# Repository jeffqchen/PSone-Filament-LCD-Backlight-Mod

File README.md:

# PSone Filament LCD Backlight Mod

The official PSone LCD screen has a fragile backlight system. The inverter and the CCFL tube could kick the bucket on itself. Sometimes you can't even figure out what went wrong with the backlight system. It's also nearly impossible to find the exact replacement parts at a reasonable price, even if you managed to figure it out.

Previously, there were multiple attempts of similar mods. But they all used singular LEDs, and resulted in uneven backlight that's difficult to look at. This new type of flexible filament LED provides the uniformity as good as the CCFL tube, and is very easy to manipulate. More importantly, they are very affordable.

So here is my solution, just in case you are facing the dilemma (however, by all means, please try to diagnose and fix the original system if possible).

This design takes the 7.5V from the power input, runs it through an NPN amplifier, to feed power through two 3V flexible filament LED strips and some current-limiting resistors, controlled by the 5V_CON signal from the console.

Please note these values were fine tuned and do not match the perfect calculations. Somehow these filament LED strips do not drop the claimed voltage and I had to reduce the value of the current-limiting resistors to make them emit enough light. I did let the system run for an extended period of time to make sure it would last. The operation temperature was still much lower than the original design.

----------
## Parts

- [PCB](https://oshpark.com/shared_projects/M3fZRLg5)

- BSR14 NPN Amplifier / SOT23-3 - [Link](https://github.com/jeffqchen/JeffParts/blob/main/Components/BSR14%20NPN%20Amplifier/info.md)

- [2x] Flexible Filament LED Strips, 130mm, DC 3V, Cold White 6500K - [Link](https://github.com/jeffqchen/JeffParts/blob/main/Parts/Flexible%20Filament%20LED/info.md)

- 2.54mm-Pitched Pin Header, Right Angle  - [Link](https://github.com/jeffqchen/JeffParts/blob/main/Connectors/Pin%20Header/2.54mm%20Pitch/Male%20Right-Angle/info.md)

**All resistors are 1/4W through hole resistors.**

- R1-3: 48 Ohm
- R4, R5: 1.2K Ohm

----------
## PCB Assembly

Nothing is special about populating the parts.

Make sure the right-angled pin headers are on the invisible side of the PCB.

Only two pins are necessary on each side of the PCB.

Note you need 3 pins in a row but have to skip the middle one. You might want to cut off the middle one before hand.

Cut and remove the black spacer after the pins are soldered in place.

Trim the legs somewhat so they don't reach too far into the main PCB when installed.

----------
## PSone Screen Motherboard Modding

- Remove component C114, C116, C117, T1
- Cut the thick trace next to CN3 marked with a cross.

----------
## Installing Mod PCB

Solder the pin headers to the inside of the motherboard as shown in the photo.

Solder two jumper wires as shown in the photo.

Solder a wire to test point DC_CON on the motherboard, and solder the other end to the DC_CON on the mod board, as indicated in the photo.

----------
## Modding Backlight Assembly

Solder TWO flexible filament LEDs in series with a 60mm-long wire connecting them in the middle.

The polarity of the LED strips is important and requires attention.

Disassemble the screen, and open up the backlight box assembly.

**VERY CAREFULLY** remove the CCFL tube.

-----------
### To Reuse The Original CCFL Plug

Desolder the plug from the tube.

*Store the CCFL in a rigid environment so it doesn't have the chance to break.*

Solder the red wire to the positive end of the LED filament in series, and the white wire to the negative end of the other LED.

*If you decided not to use the original CCFL plug, solder the positive end to the upper pin on the mod board with a piece of wire, and the negative end to the lower one with another.*

-----------

Fit the new LED assembly back into the backlight box like the original, then reassemble the entire LCD screen assembly.

----------
## Reassembly

Reseat the screen into the shell.

Reseat the motherboard onto the back of the screen assembly, then plug in the screen ribbon cable and lock the tab. Plug back in the screen backlight header.

To safely test the machine, secure the motherboard with at least two screws so the screen doesn't fall apart and cause damage.

----------
## Result

The backlight should now work. The backlight will not turn on until the PSone is powered on, exactly like how the screen is supposed to work.

The uniformity of the new backlight should be great - exactly like the original CCFL.

The color temperature of these filament LEDs is different from the original, as compared below. Personally I think the original CCFL was too blue and the LEDs look more natural.

----------
## Special Thanks

### [Zaxour](https://twitter.com/zaxour)
- For his original circuit design for the PSone LED mod - [Link](https://github.com/zaxour/PsOne_LEDBoard)

----------
Shield: [![CC BY-SA 4.0][cc-by-sa-shield]][cc-by-sa]

This work is licensed under a
[Creative Commons Attribution-ShareAlike 4.0 International License][cc-by-sa].

[![CC BY-SA 4.0][cc-by-sa-image]][cc-by-sa]

[cc-by-sa]: http://creativecommons.org/licenses/by-sa/4.0/
[cc-by-sa-image]: https://licensebuttons.net/l/by-sa/4.0/88x31.png
[cc-by-sa-shield]: https://img.shields.io/badge/License-CC%20BY--SA%204.0-lightgrey.svg

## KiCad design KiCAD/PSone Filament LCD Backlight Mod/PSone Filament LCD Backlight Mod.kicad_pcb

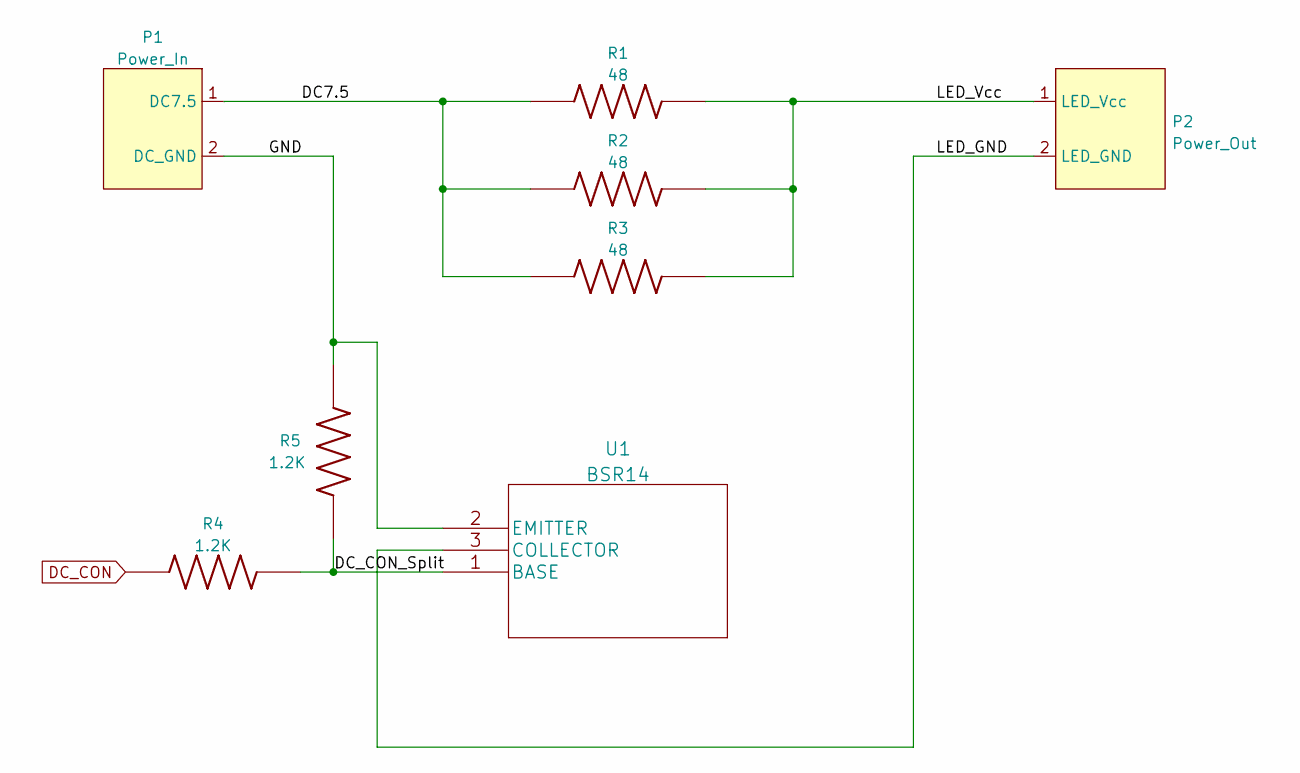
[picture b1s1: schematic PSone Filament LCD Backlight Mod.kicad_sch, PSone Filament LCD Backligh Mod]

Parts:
P1: Power_In; DC75IN
P2: Power_Out; LED_PWR
R1, R2, R3: 48; THT_Resistor
R4, R5: 1.2K; THT_Resistor
U1: BSR14

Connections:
/DC7.5: P1.1 (DC7.5), R1.1, R2.1, R3.1
/DC_CON_Split: R4.2, R5.1, U1.1 (BASE)
/GND: P1.2 (DC_GND), R5.2, U1.2 (EMITTER)
/LED_GND: P2.2 (LED_GND), U1.3 (COLLECTOR)
/LED_Vcc: P2.1 (LED_Vcc), R1.2, R2.2, R3.2
DC_CON: R4.1

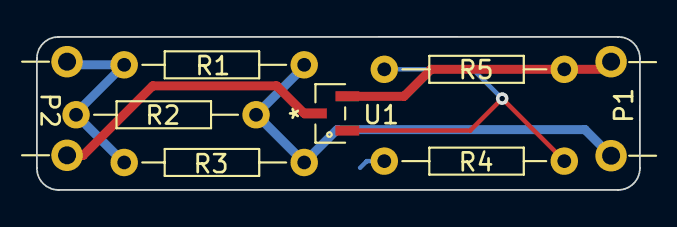
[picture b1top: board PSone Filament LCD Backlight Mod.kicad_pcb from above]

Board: 2 copper layers, 33.5 x 8.5 mm, 8 parts (0 on the bottom side), 5 nets.

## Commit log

2022-08-21 Initial files
2022-08-21 Readme writeup
2022-08-21 Add license

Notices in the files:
parts and their libraries:
Copyright 2021 Accelerated Designs. All rights reserved.
